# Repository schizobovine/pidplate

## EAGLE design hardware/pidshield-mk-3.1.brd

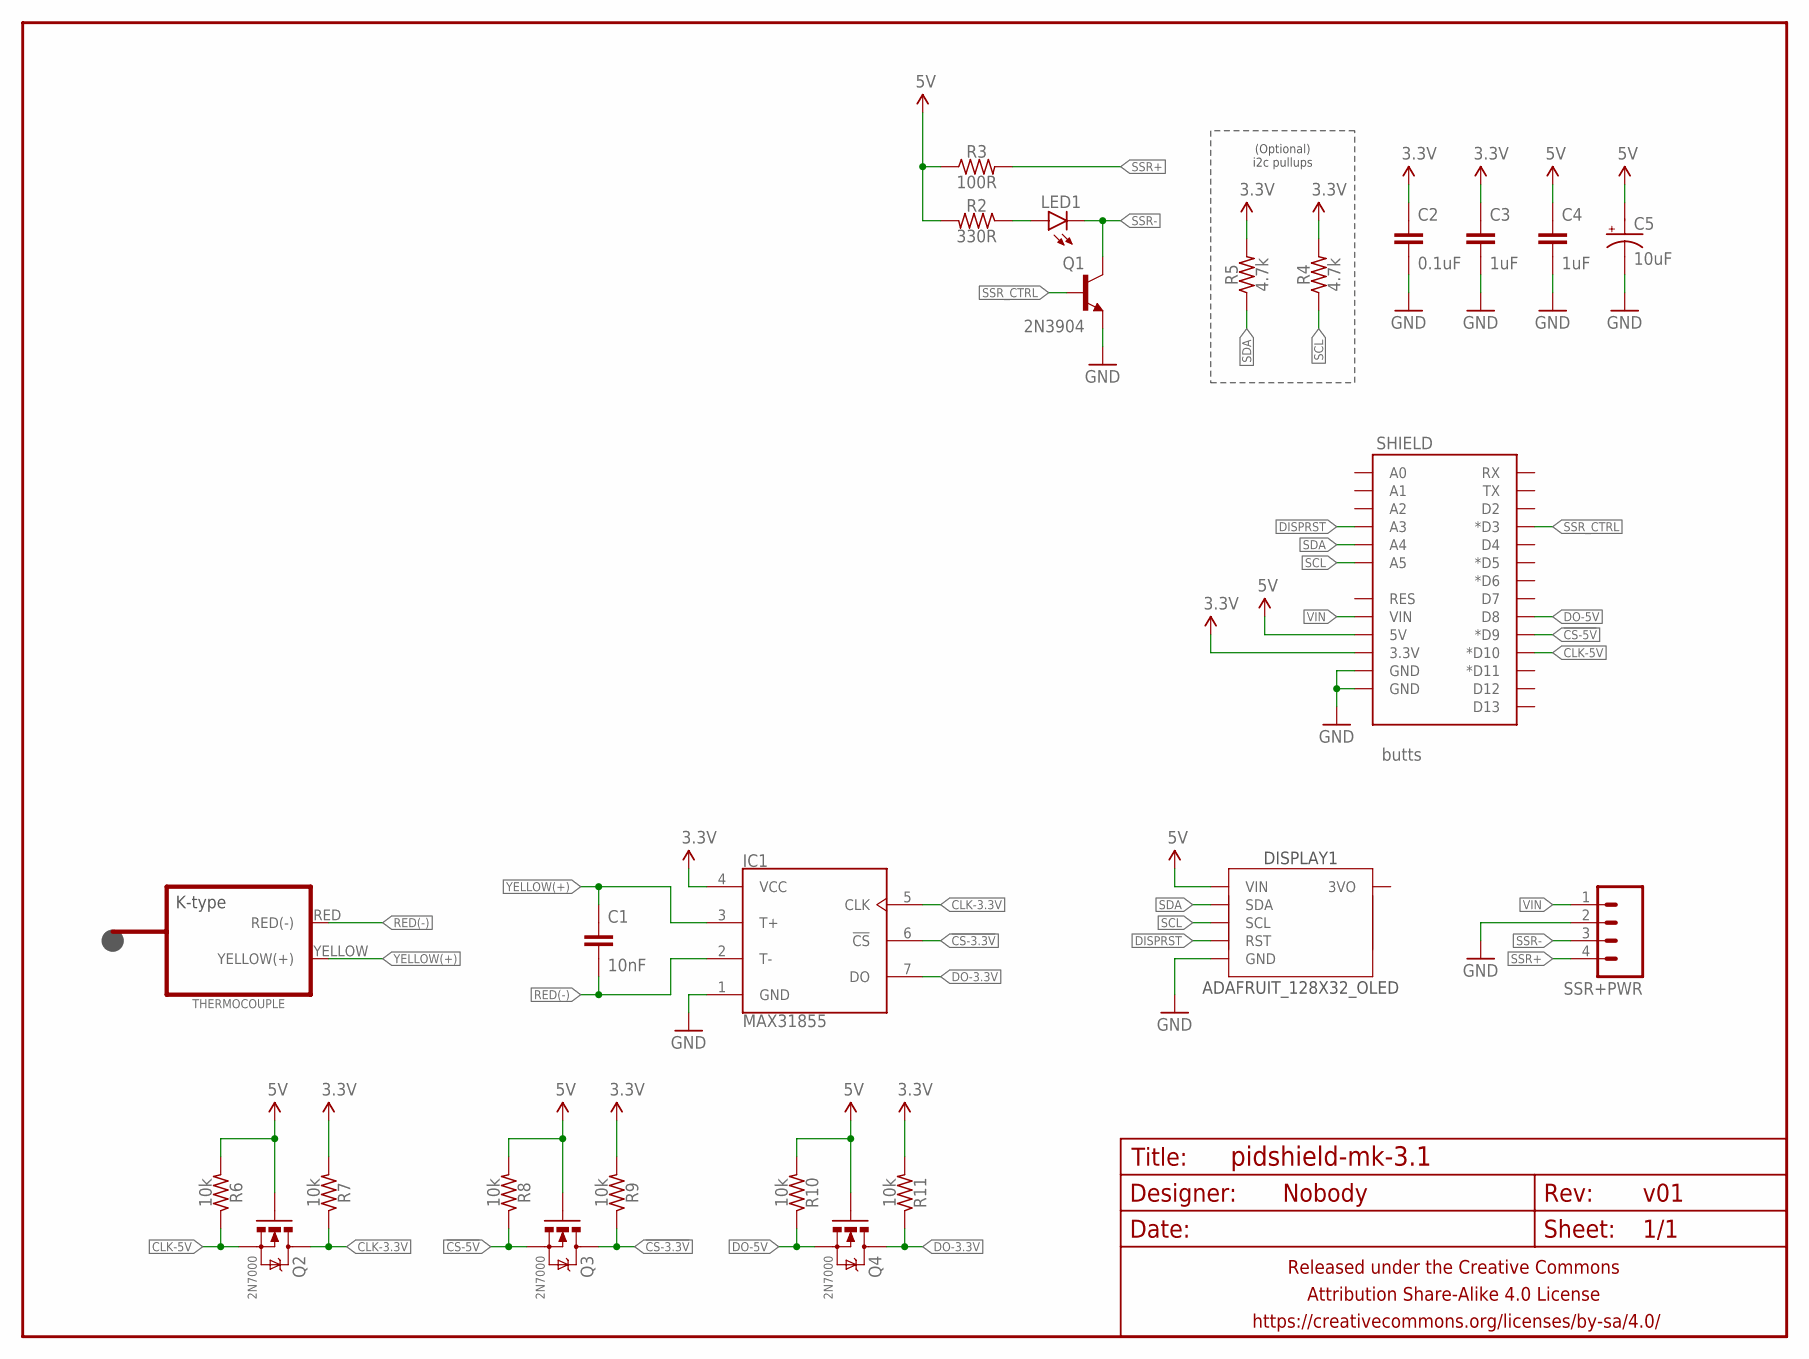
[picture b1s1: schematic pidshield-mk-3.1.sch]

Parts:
C1: 10nF; C0805
C2: 0.1uF; C025-024X044
C3, C4: 1uF; C025-024X044
C5: 10uF; E2,5-6
DISPLAY1: ADAFRUIT_128X32_OLED; ADAFRUIT_128X32_OLED_I2C_CLOSER_NOTITLE
FRAME1: FRAME-LETTERNO_PACKAGE; DUMMY
IC1: MAX31855; SOIC127P600X175-8N
LED1: LED3MM-LESS; LED3MM-LESSSILK
Q1: 2N3904; TO-92-AMMO
Q2, Q3, Q4: 2N7000; TO-92-AMMO
R2: 330R; RESISTOR-AXIAL-PTH-7.62MM
R3: 100R; RESISTOR-AXIAL-PTH-7.62MM
R4, R5: 4.7k; RESISTOR-AXIAL-PTH-7.62MM
R6, R7, R8, R9, R10, R11: 10k; RESISTOR-AXIAL-PTH-7.62MM
SHIELD: butts; ARDUINO_SHIELD_SMALLER_NEKKID
SSR+PWR: M04JST_XH_RA; JST-4-XH-RA-PTH
THERMOCOUPLE: THERMOCOUPLE-CONNECTORMINI-PCB; PCC-SMP

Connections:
3.3V: C2.1, C3.1, IC1.4 (VCC), R4.P$2 (2), R5.P$2 (2), R7.P$2 (2), R9.P$2 (2), R11.P$2 (2), SHIELD.3.3V
5V: C4.1, C5.+, DISPLAY1.VIN, Q2.2 (G), Q3.2 (G), Q4.2 (G), R2.P$2 (2), R3.P$1 (1), R6.P$2 (2), R8.P$2 (2), R10.P$2 (2), SHIELD.5V
!CS-3.3V: IC1.6 (!CS), Q3.3 (D), R9.P$1 (1)
!CS-5V: Q3.1 (S), R8.P$1 (1), SHIELD.D9 (*D9)
CLK-3.3V: IC1.5 (CLK), Q2.3 (D), R7.P$1 (1)
CLK-5V: Q2.1 (S), R6.P$1 (1), SHIELD.D10 (*D10)
DISPRST: DISPLAY1.RST, SHIELD.A3
DO-3.3V: IC1.7 (DO), Q4.3 (D), R11.P$1 (1)
DO-5V: Q4.1 (S), R10.P$1 (1), SHIELD.D8
GND: C2.2, C3.2, C4.2, C5.-, DISPLAY1.GND, IC1.1 (GND), Q1.1 (E), SHIELD.GND@0 (GND), SHIELD.GND@1 (GND), SSR+PWR.2
unnamed: LED1.A, R2.P$1 (1)
RED(-): C1.2, IC1.2 (T-), THERMOCOUPLE.RED (RED(-))
SCL: DISPLAY1.SCL, R4.P$1 (1), SHIELD.A5
SDA: DISPLAY1.SDA, R5.P$1 (1), SHIELD.A4
SSR+: R3.P$2 (2), SSR+PWR.4
SSR-: LED1.K (C), Q1.3 (C), SSR+PWR.3
SSR_CTRL: Q1.2 (B), SHIELD.D3 (*D3)
VIN: SHIELD.VIN, SSR+PWR.1
YELLOW(+): C1.1, IC1.3 (T+), THERMOCOUPLE.YELLOW (YELLOW(+))

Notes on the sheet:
(Optional) i2c pullups

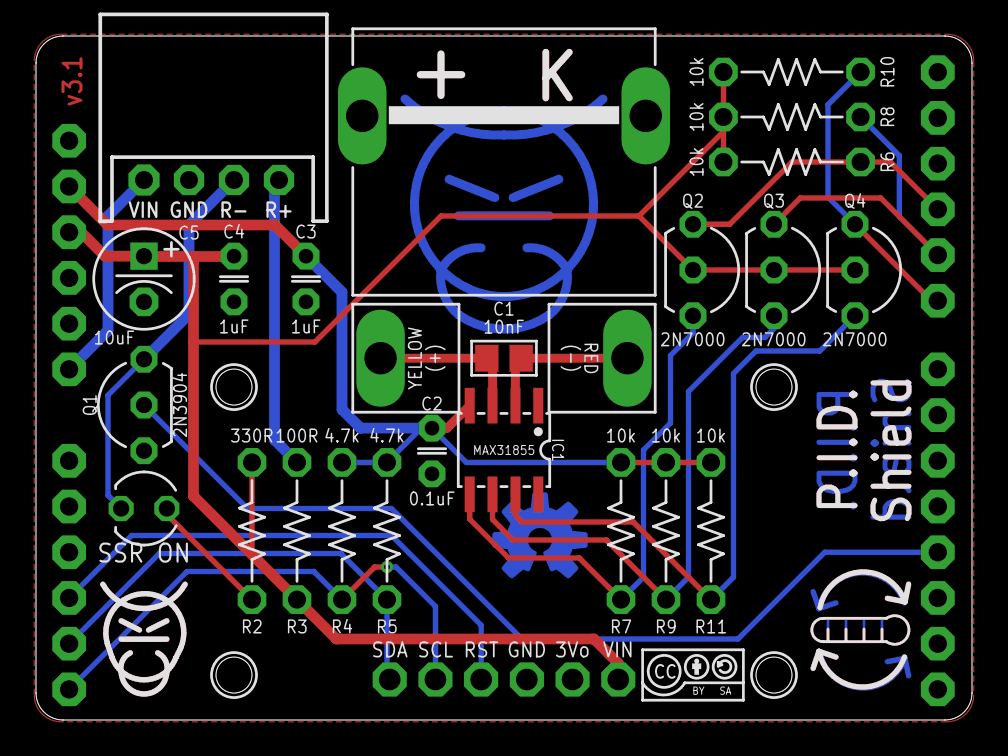
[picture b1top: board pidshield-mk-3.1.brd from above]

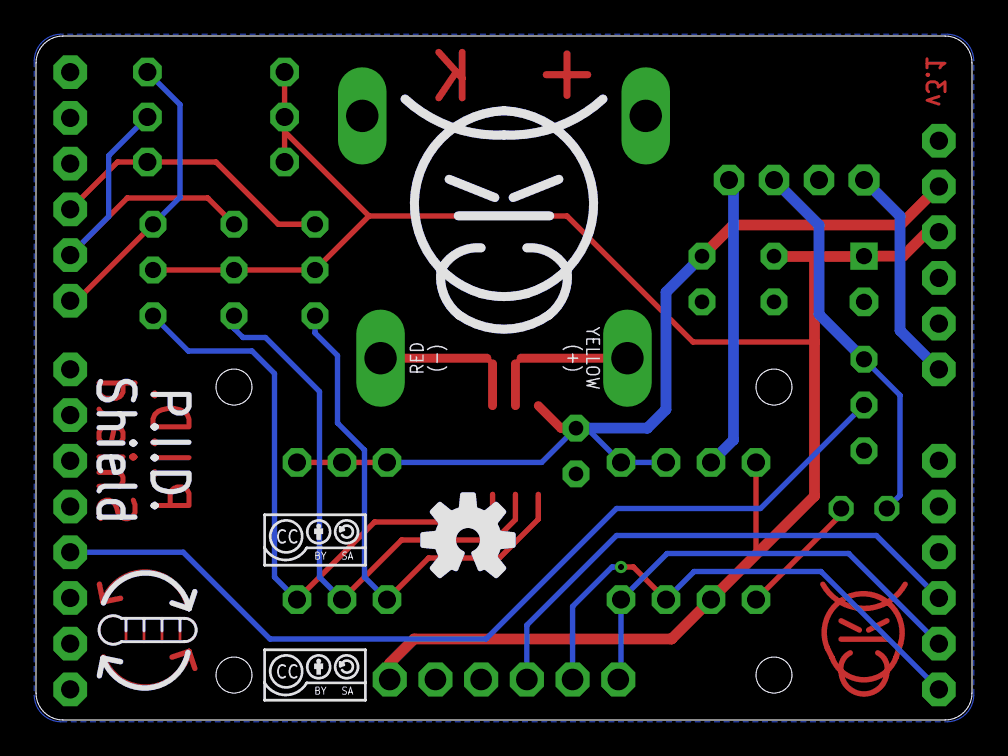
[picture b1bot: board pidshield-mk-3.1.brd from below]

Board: 2 copper layers, 52.0 x 38.0 mm, 34 parts (4 on the bottom side), 19 nets.

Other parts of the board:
U$1: COW_METAL
U$2, U$4, U$5: CC-BY-SA-4.0-NO-URL
U$3, U$6: FEEDBACK3
U$7: OSHWLOGO_BOT_0.2_A
U$8: COW_SMALL_METAL_NOTEXT

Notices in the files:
parts and their libraries:
A_butts: Released under the Creative Commons Attribution Share-Alike 4.0 License
A_butts: https://creativecommons.org/licenses/by-sa/4.0
A_butts: Released under the Creative Commons
